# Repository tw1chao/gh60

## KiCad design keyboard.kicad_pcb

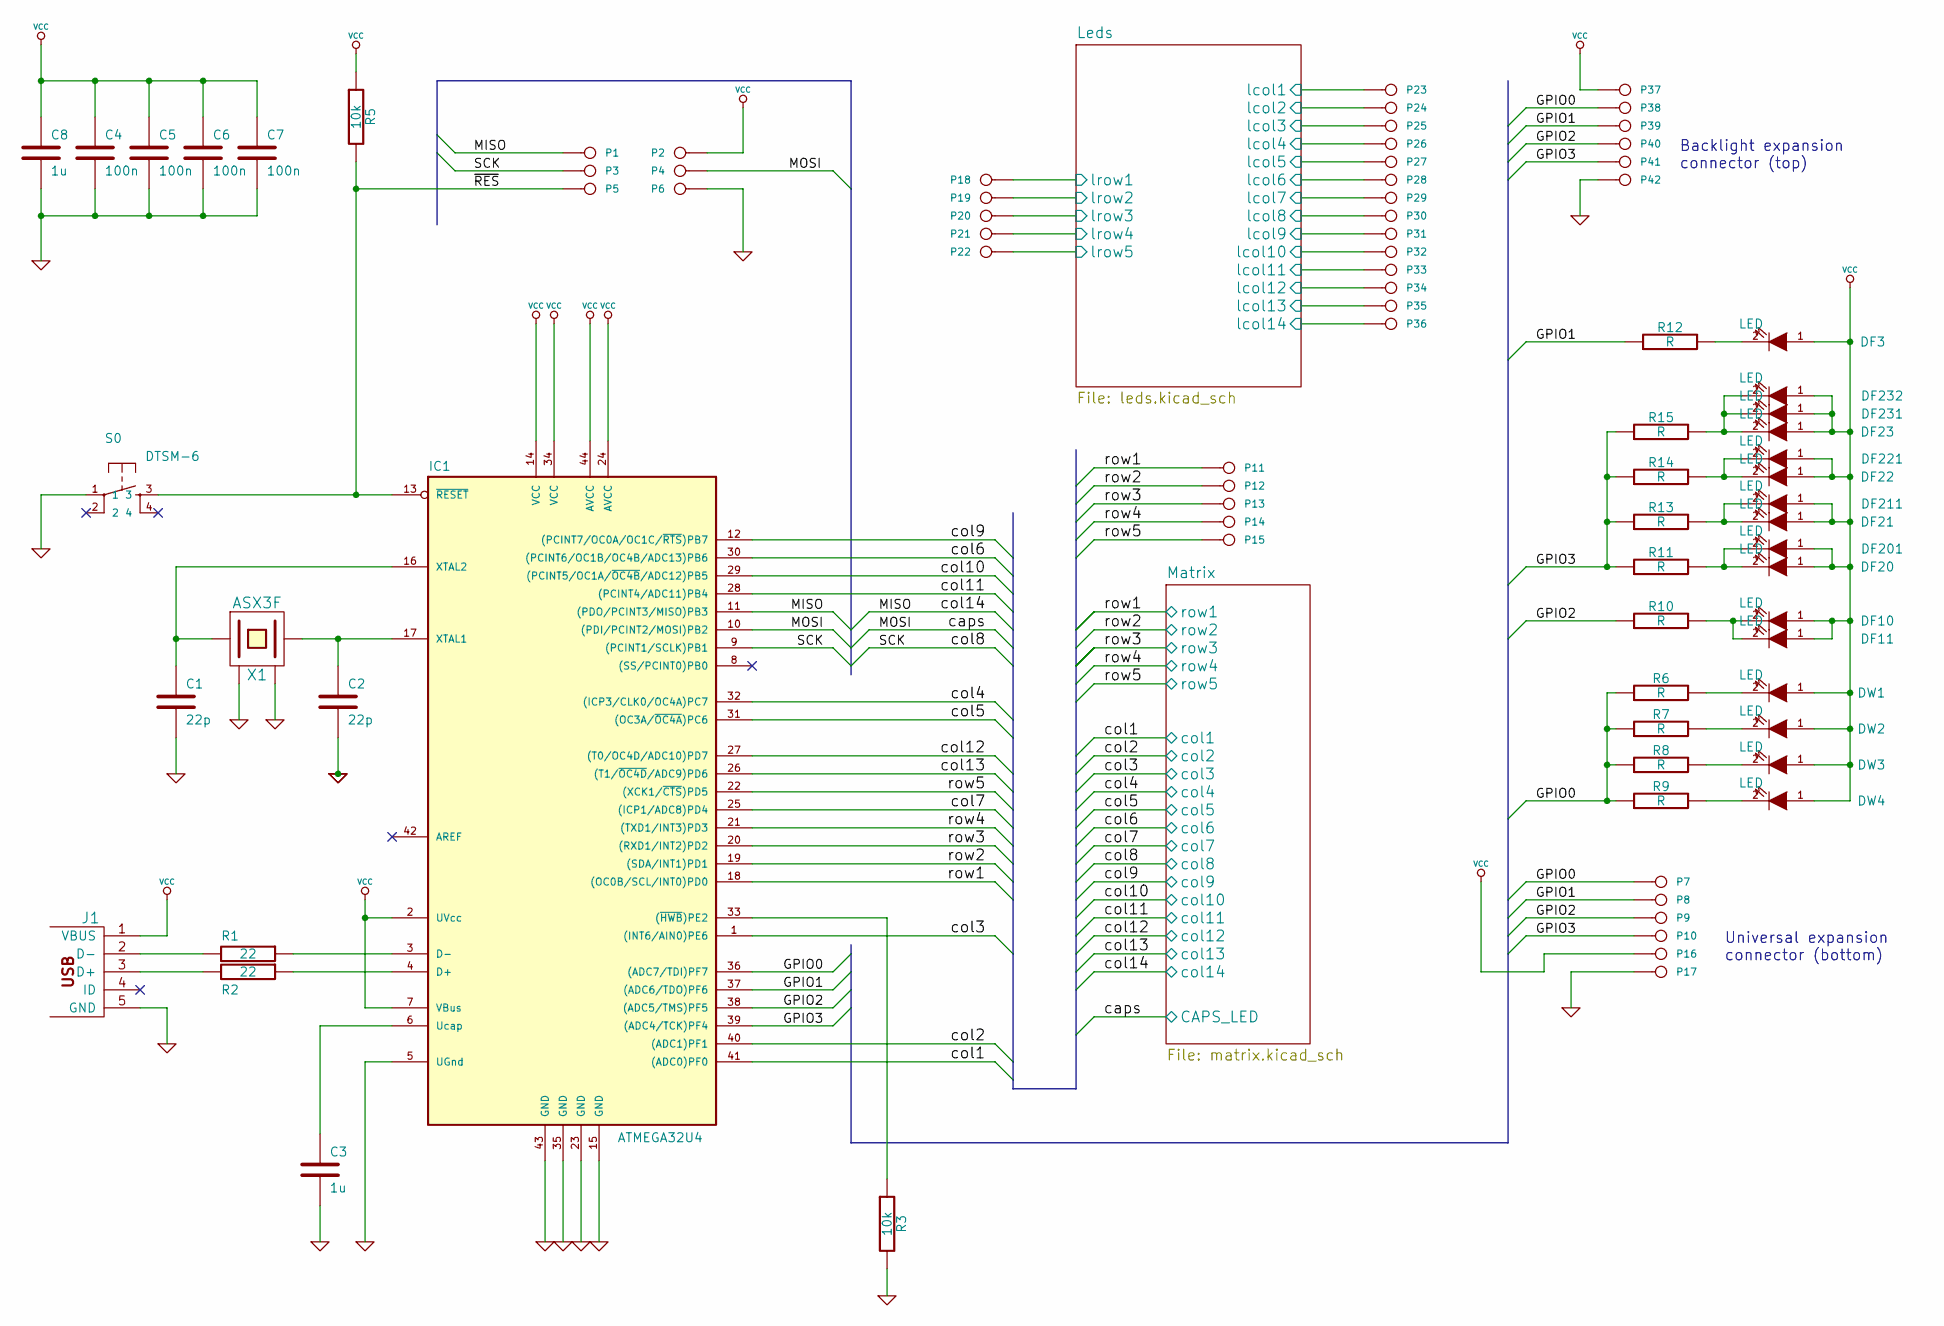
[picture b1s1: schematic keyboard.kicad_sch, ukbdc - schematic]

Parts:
C1, C2: 22p; 0805C
C3, C8: 1u; 0805C
C4, C5, C6, C7: 100n; 0805C
DF3, DF10, DF11, DF20, DF201: LED; MX1A-led_no3d
DF21, DF22, DF23, DF211, DF221, DF231, DF232: LED
DW1, DW2, DW3, DW4: LED; MX1A-led_no3d
IC1: ATMEGA32U4; TQFP44
J1: MINI; 67503
P1, P2, P3, P4, P5, P6, P7, P8, P9, P10, P11, P12, P13, P14, P15, P16, P17, P18, P19, P20, P21, P22, P23, P24, P25, P26, P27, P28, P29, P30, P31, P32, P33, P34, P35, P36, P37, P38, P39, P40, P41, P42: CONN_1
R1, R2: 22; 0805R
R3, R5: 10k; 0805R
R6, R7, R8, R9, R10, R11, R12, R13, R14, R15: R
S0: DTSM-6; KSEM31GLFS
X1: ASX3F; 4-SMD

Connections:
/GPIO0: IC1.36 ((ADC7/TDI)PF7), P7.1, P38.1, R6.1, R7.1, R8.1, R9.1
/GPIO1: IC1.37 ((ADC6/TDO)PF6), P8.1, P39.1, R12.1
/GPIO2: IC1.38 ((ADC5/TMS)PF5), P9.1, P40.1, R10.1
/GPIO3: IC1.39 ((ADC4/TCK)PF4), P10.1, P41.1, R11.1, R13.1, R14.1, R15.1
/Leds/lcol1: P23.1; also elsewhere on the board
/Leds/lcol2: P24.1; also elsewhere on the board
/Leds/lcol3: P25.1; also elsewhere on the board
/Leds/lcol4: P26.1; also elsewhere on the board
/Leds/lcol5: P27.1; also elsewhere on the board
/Leds/lcol6: P28.1; also elsewhere on the board
/Leds/lcol7: P29.1; also elsewhere on the board
/Leds/lcol8: P30.1; also elsewhere on the board
/Leds/lcol9: P31.1; also elsewhere on the board
/Leds/lcol10: P32.1; also elsewhere on the board
/Leds/lcol11: P33.1; also elsewhere on the board
/Leds/lcol12: P34.1; also elsewhere on the board
/Leds/lcol13: P35.1; also elsewhere on the board
/Leds/lcol14: P36.1; also elsewhere on the board
/Leds/lrow1: P18.1; also elsewhere on the board
/Leds/lrow2: P19.1; also elsewhere on the board
/Leds/lrow3: P20.1; also elsewhere on the board
/Leds/lrow4: P21.1; also elsewhere on the board
/Leds/lrow5: P22.1; also elsewhere on the board
/Matrix/CAPS_LED: IC1.10 ((PDI/PCINT2/MOSI)PB2), P4.1; also elsewhere on the board
/Matrix/col1: IC1.41 ((ADC0)PF0); also elsewhere on the board
/Matrix/col2: IC1.40 ((ADC1)PF1); also elsewhere on the board
/Matrix/col3: IC1.1 ((INT6/AIN0)PE6); also elsewhere on the board
/Matrix/col4: IC1.32 ((ICP3/CLK0/OC4A)PC7); also elsewhere on the board
/Matrix/col5: IC1.31 ((OC3A/~OC4A)PC6); also elsewhere on the board
/Matrix/col6: IC1.30 ((PCINT6/OC1B/OC4B/ADC13)PB6); also elsewhere on the board
/Matrix/col7: IC1.25 ((ICP1/ADC8)PD4); also elsewhere on the board
/Matrix/col8: IC1.9 ((PCINT1/SCLK)PB1), P3.1; also elsewhere on the board
/Matrix/col9: IC1.12 ((PCINT7/OC0A/OC1C/~RTS)PB7); also elsewhere on the board
/Matrix/col10: IC1.29 ((PCINT5/OC1A/~OC4B/ADC12)PB5); also elsewhere on the board
/Matrix/col11: IC1.28 ((PCINT4/ADC11)PB4); also elsewhere on the board
/Matrix/col12: IC1.27 ((T0/OC4D/ADC10)PD7); also elsewhere on the board
/Matrix/col13: IC1.26 ((T1/~OC4D/ADC9)PD6); also elsewhere on the board
/Matrix/col14: IC1.11 ((PDO/PCINT3/MISO)PB3), P1.1; also elsewhere on the board
/Matrix/row1: IC1.18 ((OC0B/SCL/INT0)PD0), P11.1; also elsewhere on the board
/Matrix/row2: IC1.19 ((SDA/INT1)PD1), P12.1; also elsewhere on the board
/Matrix/row3: IC1.20 ((RXD1/INT2)PD2), P13.1; also elsewhere on the board
/Matrix/row4: IC1.21 ((TXD1/INT3)PD3), P14.1; also elsewhere on the board
/Matrix/row5: IC1.22 ((XCK1/~CTS)PD5), P15.1; also elsewhere on the board
/~RES: IC1.13 (~RESET), P5.1, R5.2, S0.3
GND: C1.2, C2.2, C3.2, C4.2, C5.2, C6.2, C7.2, C8.2, IC1.5 (UGnd), IC1.15 (GND), IC1.23 (GND), IC1.35 (GND), IC1.43 (GND), J1.5 (GND), P6.1, P17.1, P42.1, R3.2, S0.1, X1.2 (GND), X1.4 (GND)
unnamed: C1.1, IC1.16 (XTAL2), X1.1
unnamed: DW3.2 (K), R8.2
unnamed: DW2.2 (K), R7.2
unnamed: DW1.2 (K), R6.2
unnamed: DW4.2 (K), R9.2
unnamed: IC1.33 ((~HWB)PE2), R3.1
unnamed: J1.3 (D+), R2.2
unnamed: J1.2 (D-), R1.2
unnamed: IC1.4 (D+), R2.1
unnamed: IC1.3 (D-), R1.1
unnamed: C3.1, IC1.6 (Ucap)
unnamed: C2.1, IC1.17 (XTAL1), X1.3 (2)
unnamed: DF22.2 (K), DF221.2 (K), R14.2
unnamed: DF3.2 (K), R12.2
unnamed: DF10.2 (K), DF11.2 (K), R10.2
unnamed: DF23.2 (K), DF231.2 (K), DF232.2 (K), R15.2
unnamed: DF20.2 (K), DF201.2 (K), R11.2
unnamed: DF21.2 (K), DF211.2 (K), R13.2
VCC: C4.1, C5.1, C6.1, C7.1, C8.1, DF3.1 (A), DF10.1 (A), DF11.1 (A), DF20.1 (A), DF21.1 (A), DF22.1 (A), DF23.1 (A), DF201.1 (A), DF211.1 (A), DF221.1 (A), DF231.1 (A), DF232.1 (A), DW1.1 (A), DW2.1 (A), DW3.1 (A), DW4.1 (A), IC1.2 (UVcc), IC1.7 (VBus), IC1.14 (VCC), IC1.24 (AVCC), IC1.34 (VCC), IC1.44 (AVCC), J1.1 (VBUS), P2.1, P16.1, P37.1, R5.1; also elsewhere on the board

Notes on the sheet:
Universal expansion connector (bottom)
Backlight expansion connector (top)

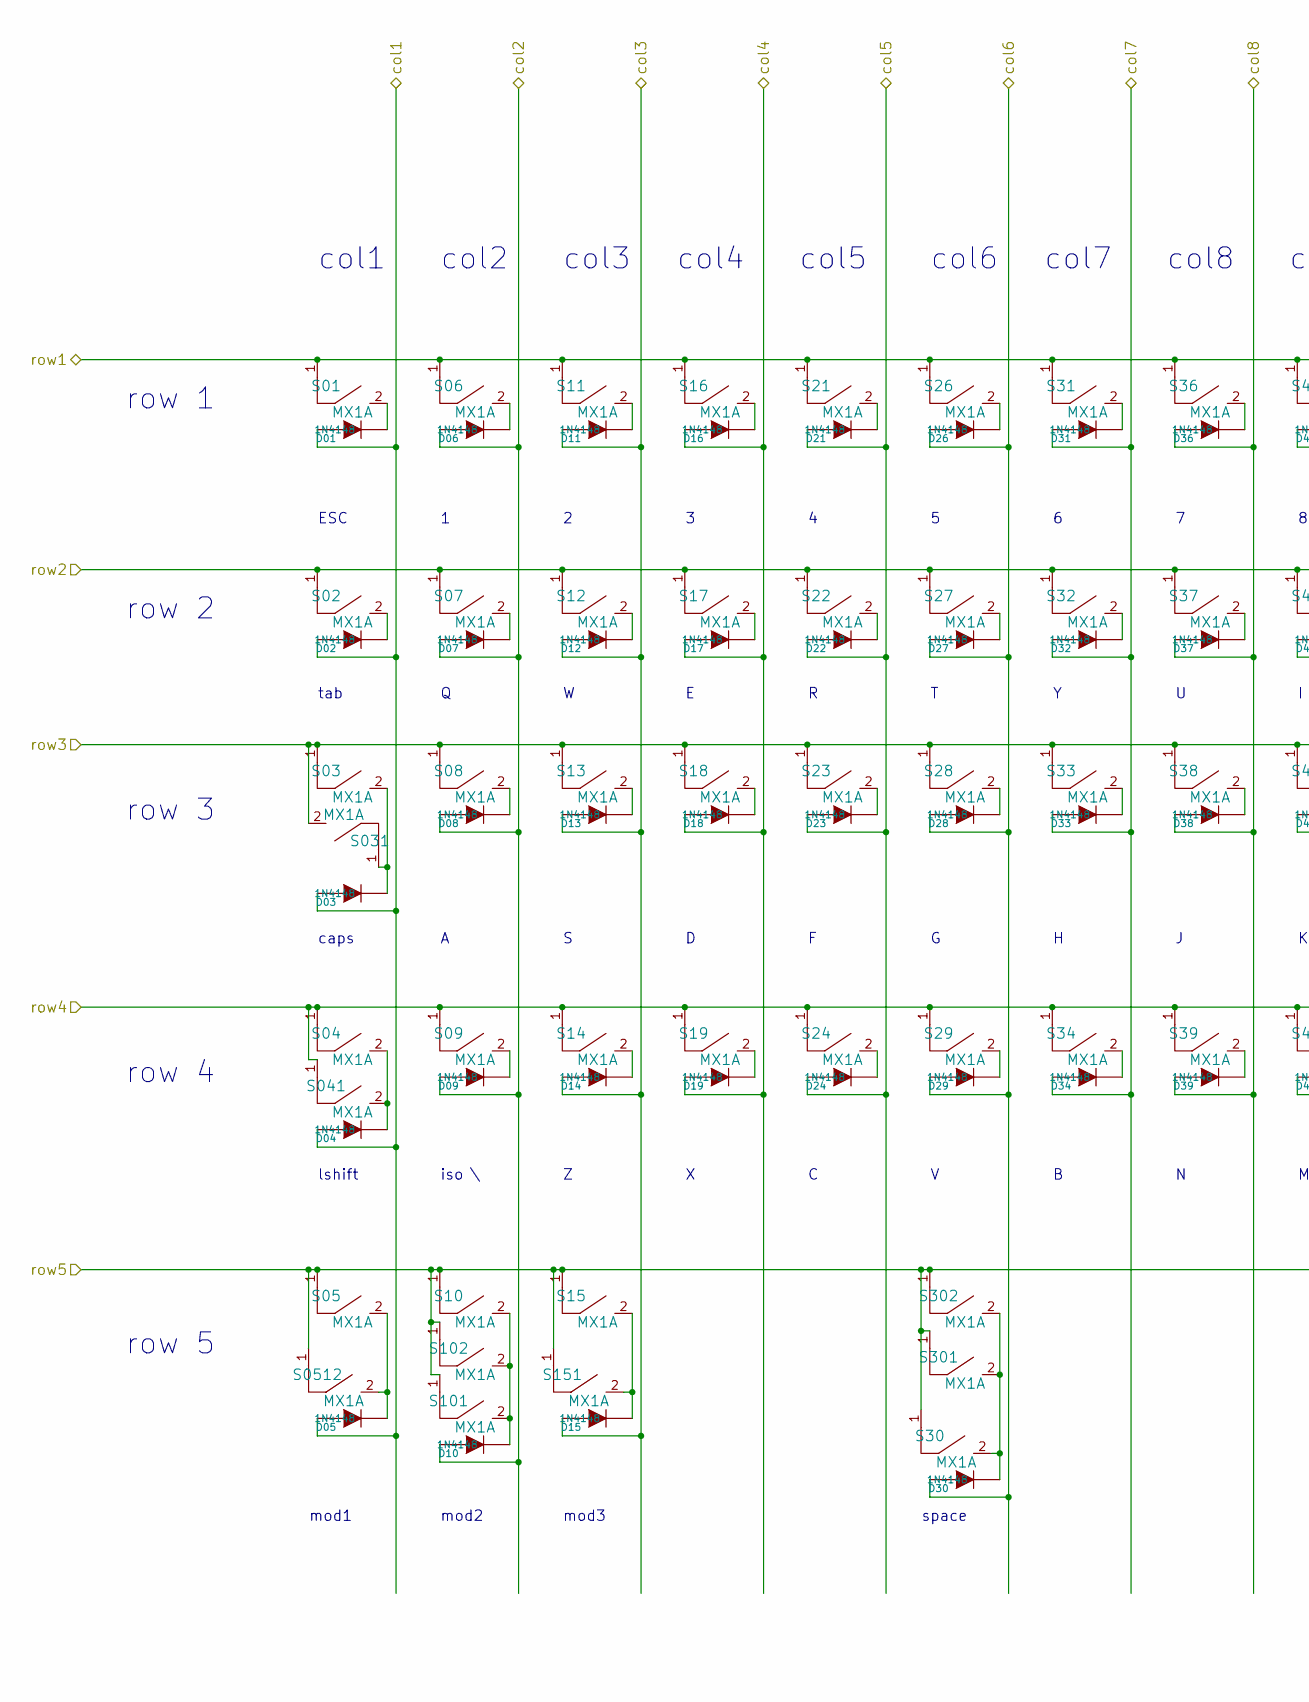
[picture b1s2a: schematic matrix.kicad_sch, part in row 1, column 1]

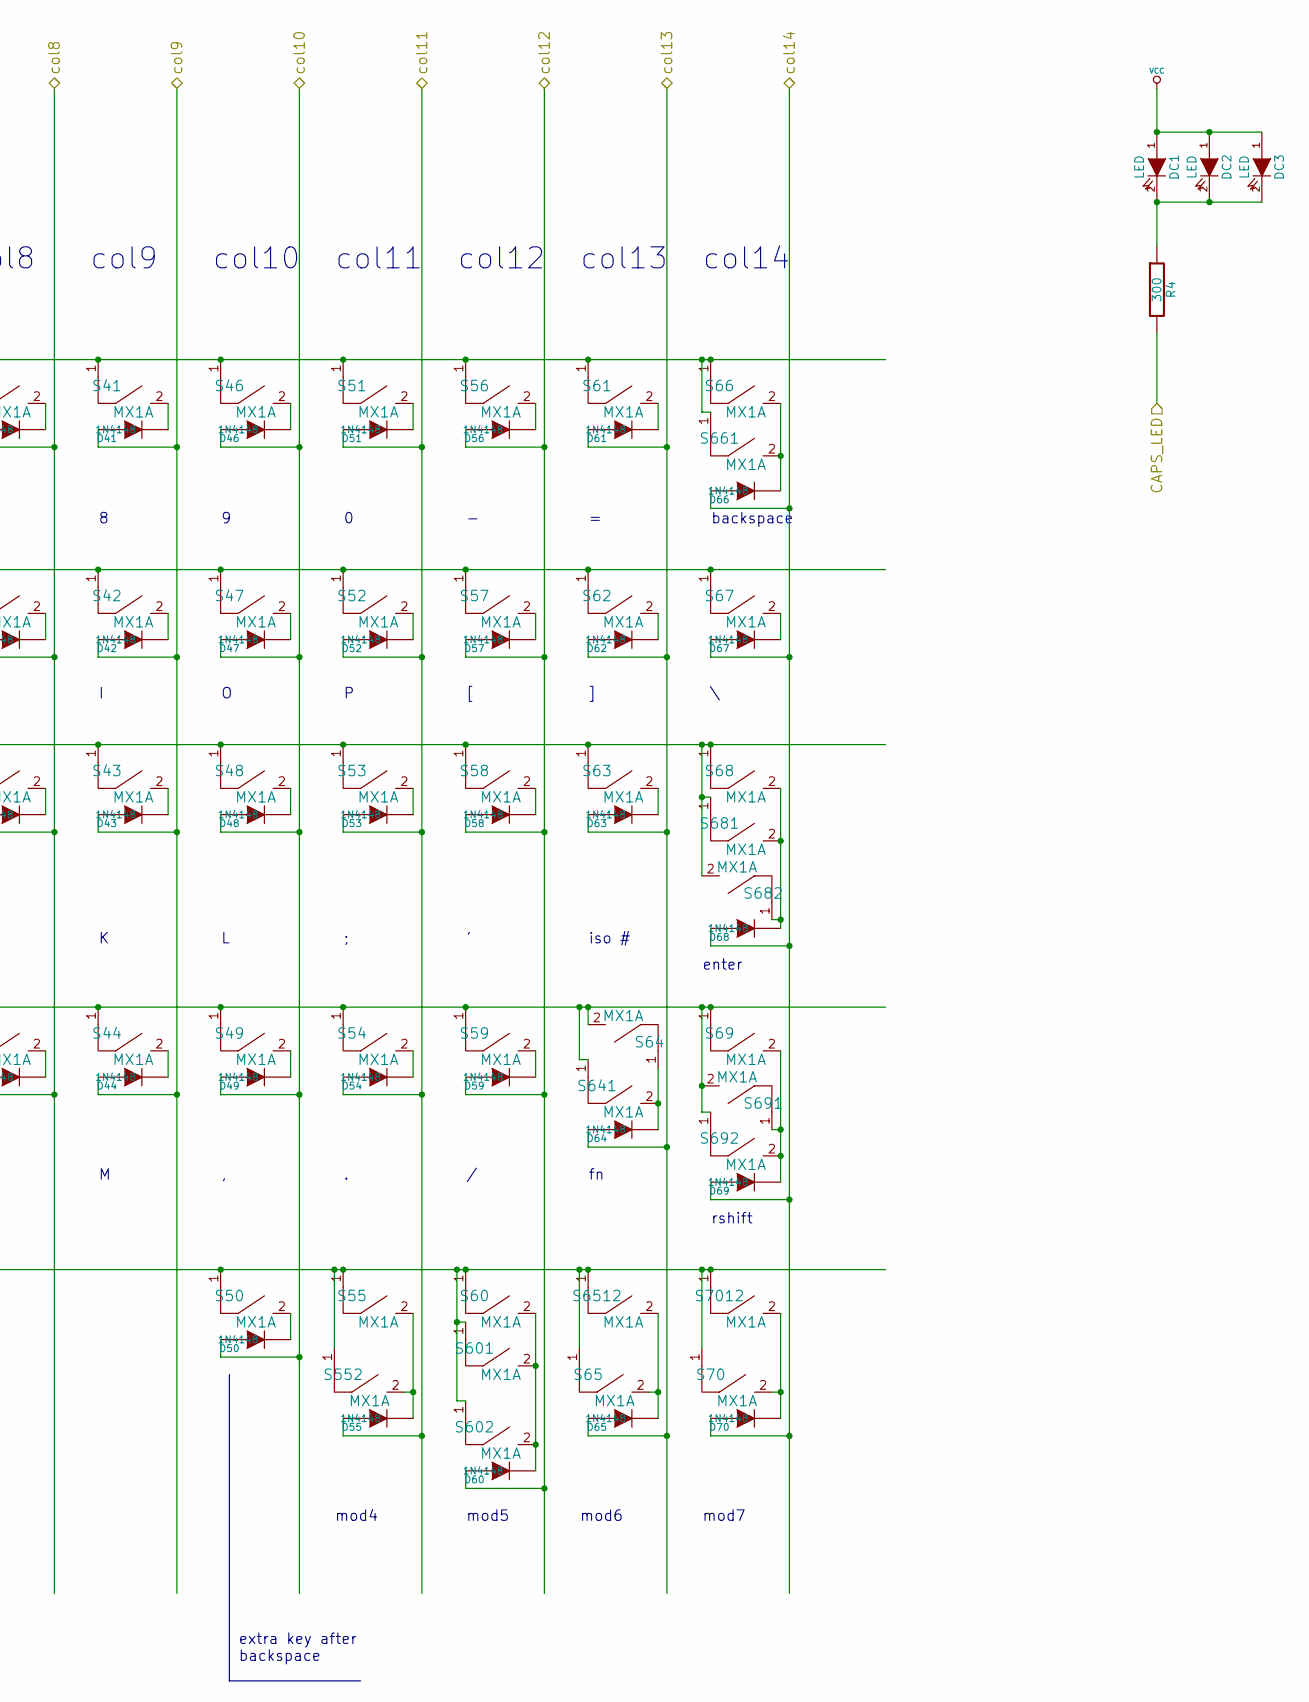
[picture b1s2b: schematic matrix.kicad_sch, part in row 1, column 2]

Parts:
D01, D02, D03, D04, D05, D06, D07, D08, D09, D10, D11, D12, D13, D14, D15, D16, D17, D18, D19, D21, D22, D23, D24, D26, D27, D28, D29, D30, D31, D32, D33, D34, D36, D37, D38, D39, D41, D42, D43, D44, D46, D47, D48, D49, D50, D51, D52, D53, D54, D55, D56, D57, D58, D59, D60, D61, D62, D63, D64, D65, D66, D67, D68, D69, D70: 1N4148; 0805D
DC1, DC2: LED; MX1A-led_no3d
DC3: LED
R4: 300
S01, S02, S03, S04, S05, S06, S07, S08, S10, S11, S12, S13, S14, S15, S16, S17, S18, S19, S21, S22, S23, S24, S26, S27, S28, S29, S30, S31, S32, S33, S34, S36, S37, S38, S39, S41, S42, S43, S44, S46, S47, S48, S49, S51, S52, S53, S54, S55, S56, S57, S58, S59, S60, S61, S62, S65, S66, S67, S68, S69, S70: MX1A
S09, S031, S041, S50, S63, S64, S101, S102, S151, S301, S302, S0512, S552, S601, S602, S641, S661, S681, S682, S691, S692, S6512, S7012: MX1A; MX1A_no3d

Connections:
/Matrix/CAPS_LED: R4.2; also elsewhere on the board
/Matrix/col1: D01.1 (A), D02.1 (A), D03.1 (A), D04.1 (A), D05.1 (A); also elsewhere on the board
/Matrix/col2: D06.1 (A), D07.1 (A), D08.1 (A), D09.1 (A), D10.1 (A); also elsewhere on the board
/Matrix/col3: D11.1 (A), D12.1 (A), D13.1 (A), D14.1 (A), D15.1 (A); also elsewhere on the board
/Matrix/col4: D16.1 (A), D17.1 (A), D18.1 (A), D19.1 (A); also elsewhere on the board
/Matrix/col5: D21.1 (A), D22.1 (A), D23.1 (A), D24.1 (A); also elsewhere on the board
/Matrix/col6: D26.1 (A), D27.1 (A), D28.1 (A), D29.1 (A), D30.1 (A); also elsewhere on the board
/Matrix/col7: D31.1 (A), D32.1 (A), D33.1 (A), D34.1 (A); also elsewhere on the board
/Matrix/col8: D36.1 (A), D37.1 (A), D38.1 (A), D39.1 (A); also elsewhere on the board
/Matrix/col9: D41.1 (A), D42.1 (A), D43.1 (A), D44.1 (A); also elsewhere on the board
/Matrix/col10: D46.1 (A), D47.1 (A), D48.1 (A), D49.1 (A), D50.1 (A); also elsewhere on the board
/Matrix/col11: D51.1 (A), D52.1 (A), D53.1 (A), D54.1 (A), D55.1 (A); also elsewhere on the board
/Matrix/col12: D56.1 (A), D57.1 (A), D58.1 (A), D59.1 (A), D60.1 (A); also elsewhere on the board
/Matrix/col13: D61.1 (A), D62.1 (A), D63.1 (A), D64.1 (A), D65.1 (A); also elsewhere on the board
/Matrix/col14: D66.1 (A), D67.1 (A), D68.1 (A), D69.1 (A), D70.1 (A); also elsewhere on the board
/Matrix/row1: S01.1, S06.1, S11.1, S16.1, S21.1, S26.1, S31.1, S36.1, S41.1, S46.1, S51.1, S56.1, S61.1, S66.1, S661.1; also elsewhere on the board
/Matrix/row2: S02.1, S07.1, S12.1, S17.1, S22.1, S27.1, S32.1, S37.1, S42.1, S47.1, S52.1, S57.1, S62.1, S67.1; also elsewhere on the board
/Matrix/row3: S03.1, S08.1, S13.1, S18.1, S23.1, S28.1, S031.2, S33.1, S38.1, S43.1, S48.1, S53.1, S58.1, S63.1, S68.1, S681.1, S682.2; also elsewhere on the board
/Matrix/row4: S04.1, S09.1, S14.1, S19.1, S24.1, S29.1, S34.1, S39.1, S041.1, S44.1, S49.1, S54.1, S59.1, S64.2, S69.1, S641.1, S691.2, S692.1; also elsewhere on the board
/Matrix/row5: S05.1, S10.1, S15.1, S30.1, S50.1, S55.1, S60.1, S65.1, S70.1, S101.1, S102.1, S151.1, S301.1, S302.1, S0512.1, S552.1, S601.1, S602.1, S6512.1, S7012.1; also elsewhere on the board
unnamed: D16.2 (K), S16.2
unnamed: D27.2 (K), S27.2
unnamed: D28.2 (K), S28.2
unnamed: D29.2 (K), S29.2
unnamed: D17.2 (K), S17.2
unnamed: D18.2 (K), S18.2
unnamed: D19.2 (K), S19.2
unnamed: D41.2 (K), S41.2
unnamed: D37.2 (K), S37.2
unnamed: D38.2 (K), S38.2
unnamed: D22.2 (K), S22.2
unnamed: D43.2 (K), S43.2
unnamed: D42.2 (K), S42.2
unnamed: D46.2 (K), S46.2
unnamed: D47.2 (K), S47.2
unnamed: D23.2 (K), S23.2
unnamed: D21.2 (K), S21.2
unnamed: D31.2 (K), S31.2
unnamed: D01.2 (K), S01.2
unnamed: D33.2 (K), S33.2
unnamed: D32.2 (K), S32.2
unnamed: D36.2 (K), S36.2
unnamed: D05.2 (K), S05.2, S0512.2
unnamed: D15.2 (K), S15.2, S151.2
unnamed: D55.2 (K), S55.2, S552.2
unnamed: D51.2 (K), S51.2
unnamed: D65.2 (K), S65.2, S6512.2
unnamed: D12.2 (K), S12.2
unnamed: D02.2 (K), S02.2
unnamed: D07.2 (K), S07.2
unnamed: D08.2 (K), S08.2
unnamed: D13.2 (K), S13.2
unnamed: D09.2 (K), S09.2
unnamed: D14.2 (K), S14.2
unnamed: D70.2 (K), S70.2, S7012.2
unnamed: D03.2 (K), S03.2, S031.1
unnamed: D26.2 (K), S26.2
unnamed: D06.2 (K), S06.2
unnamed: D11.2 (K), S11.2
unnamed: D50.2 (K), S50.2
unnamed: D63.2 (K), S63.2
unnamed: D58.2 (K), S58.2
unnamed: D53.2 (K), S53.2
unnamed: D67.2 (K), S67.2
unnamed: D52.2 (K), S52.2
unnamed: D48.2 (K), S48.2
unnamed: D44.2 (K), S44.2
unnamed: D62.2 (K), S62.2
unnamed: D49.2 (K), S49.2
unnamed: D54.2 (K), S54.2
unnamed: D59.2 (K), S59.2
unnamed: D57.2 (K), S57.2
unnamed: D61.2 (K), S61.2
unnamed: D56.2 (K), S56.2
unnamed: D24.2 (K), S24.2
unnamed: D34.2 (K), S34.2
unnamed: D39.2 (K), S39.2
unnamed: D68.2 (K), S68.2, S681.2, S682.1
unnamed: D10.2 (K), S10.2, S101.2, S102.2
unnamed: D30.2 (K), S30.2, S301.2, S302.2
unnamed: D04.2 (K), S04.2, S041.2
unnamed: D64.2 (K), S64.1, S641.2
unnamed: D69.2 (K), S69.2, S691.1, S692.2
unnamed: DC1.2 (K), DC2.2 (K), DC3.2 (K), R4.1
unnamed: D60.2 (K), S60.2, S601.2, S602.2
unnamed: D66.2 (K), S66.2, S661.2
VCC: DC1.1 (A), DC2.1 (A), DC3.1 (A); also elsewhere on the board

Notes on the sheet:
space
col6
ESC
mod5
col5
col13
col10
col4
row 4
mod7
lshift
iso \
tab
col12
mod1
mod4
iso #
rshift
row 1
enter
col14
col8
col11
mod2
col7
col2
backspace
extra key after backspace
col1
row 2
row 5
col3
mod3
caps
col9
mod6
row 3

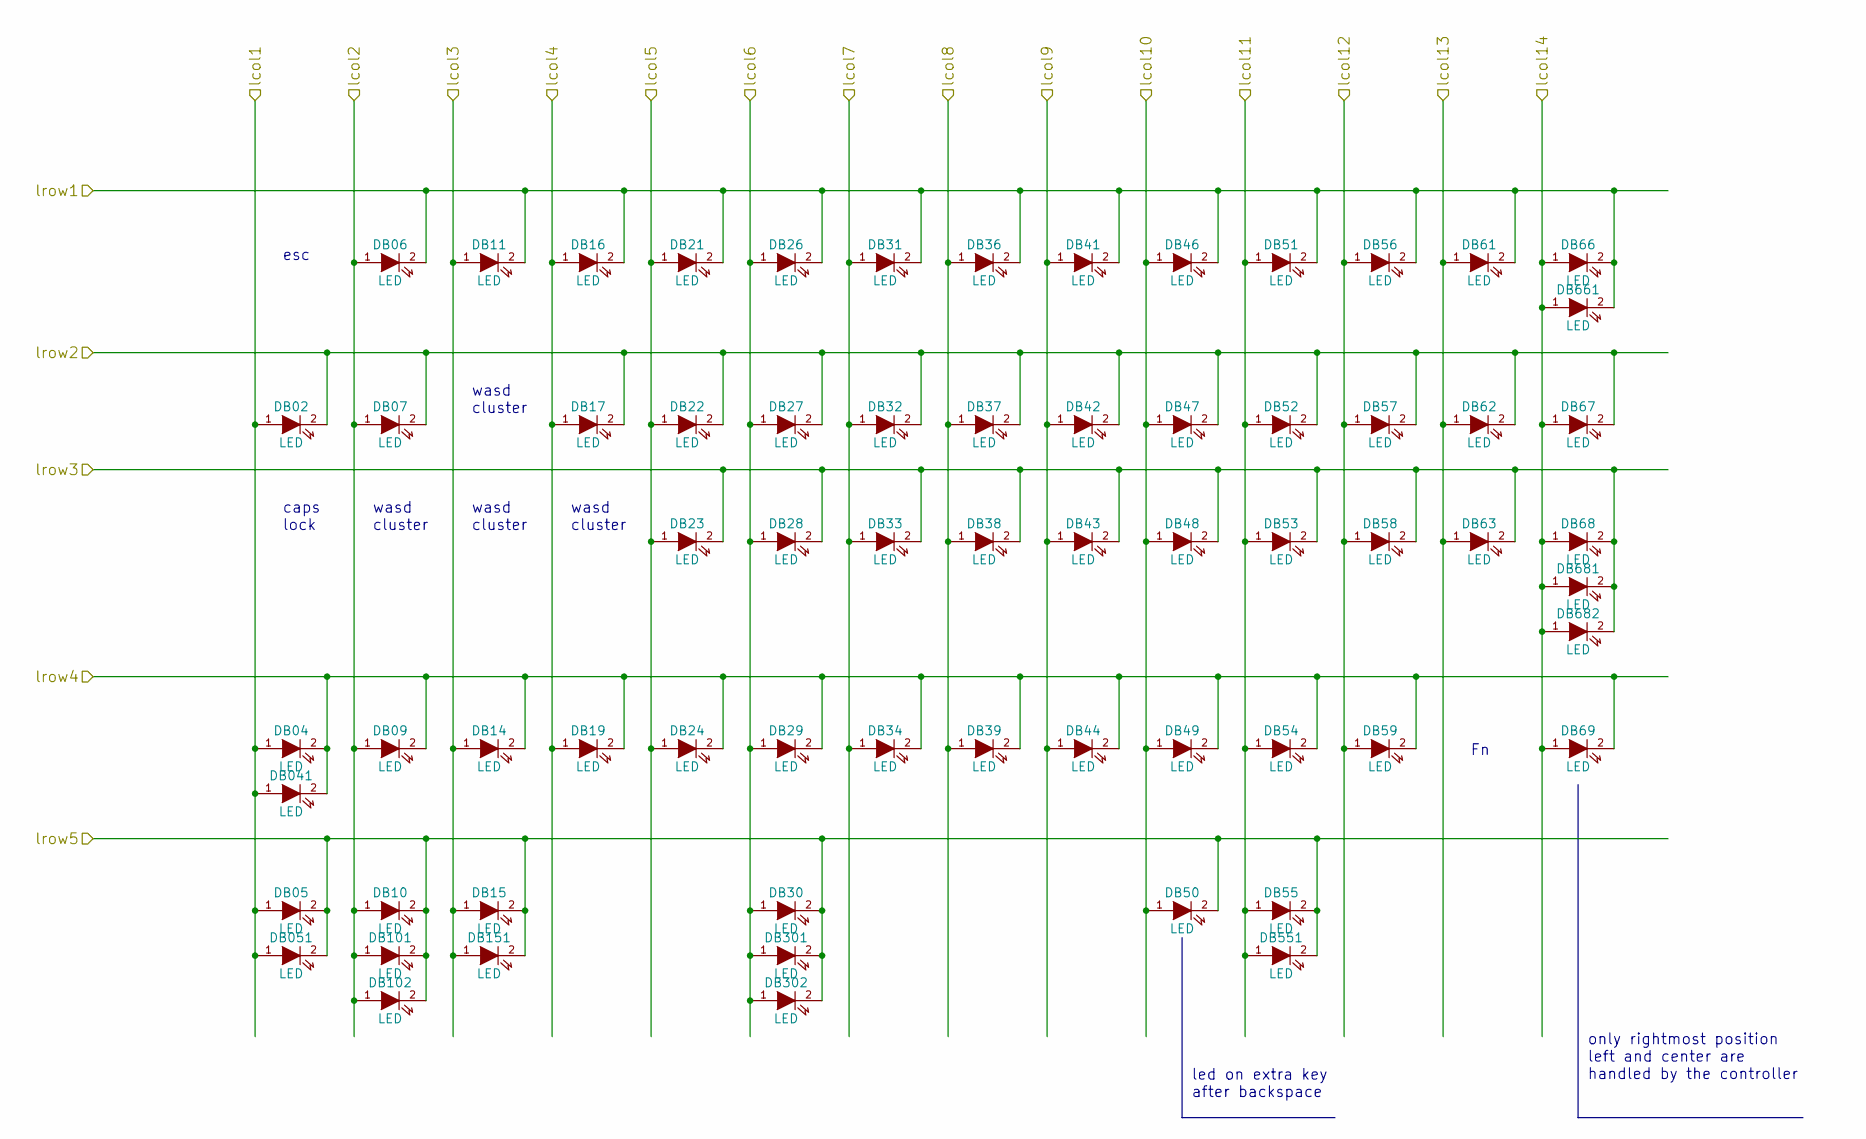
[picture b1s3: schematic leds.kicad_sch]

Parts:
DB02, DB04, DB06, DB07, DB09, DB11, DB14, DB16, DB17, DB19, DB21, DB22, DB23, DB24, DB26, DB27, DB28, DB29, DB30, DB31, DB32, DB33, DB34, DB36, DB37, DB38, DB39, DB41, DB041, DB42, DB43, DB44, DB46, DB47, DB48, DB49, DB50, DB51, DB52, DB53, DB54, DB56, DB57, DB58, DB59, DB61, DB62, DB63, DB66, DB67, DB68, DB69, DB301, DB302, DB661, DB681, DB682: LED; MX1A-led_no3d
DB05, DB10, DB15, DB051, DB55, DB101, DB102, DB151, DB551: LED

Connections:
/Leds/lcol1: DB02.1 (A), DB04.1 (A), DB05.1 (A), DB041.1 (A), DB051.1 (A); also elsewhere on the board
/Leds/lcol2: DB06.1 (A), DB07.1 (A), DB09.1 (A), DB10.1 (A), DB101.1 (A), DB102.1 (A); also elsewhere on the board
/Leds/lcol3: DB11.1 (A), DB14.1 (A), DB15.1 (A), DB151.1 (A); also elsewhere on the board
/Leds/lcol4: DB16.1 (A), DB17.1 (A), DB19.1 (A); also elsewhere on the board
/Leds/lcol5: DB21.1 (A), DB22.1 (A), DB23.1 (A), DB24.1 (A); also elsewhere on the board
/Leds/lcol6: DB26.1 (A), DB27.1 (A), DB28.1 (A), DB29.1 (A), DB30.1 (A), DB301.1 (A), DB302.1 (A); also elsewhere on the board
/Leds/lcol7: DB31.1 (A), DB32.1 (A), DB33.1 (A), DB34.1 (A); also elsewhere on the board
/Leds/lcol8: DB36.1 (A), DB37.1 (A), DB38.1 (A), DB39.1 (A); also elsewhere on the board
/Leds/lcol9: DB41.1 (A), DB42.1 (A), DB43.1 (A), DB44.1 (A); also elsewhere on the board
/Leds/lcol10: DB46.1 (A), DB47.1 (A), DB48.1 (A), DB49.1 (A), DB50.1 (A); also elsewhere on the board
/Leds/lcol11: DB51.1 (A), DB52.1 (A), DB53.1 (A), DB54.1 (A), DB55.1 (A), DB551.1 (A); also elsewhere on the board
/Leds/lcol12: DB56.1 (A), DB57.1 (A), DB58.1 (A), DB59.1 (A); also elsewhere on the board
/Leds/lcol13: DB61.1 (A), DB62.1 (A), DB63.1 (A); also elsewhere on the board
/Leds/lcol14: DB66.1 (A), DB67.1 (A), DB68.1 (A), DB69.1 (A), DB661.1 (A), DB681.1 (A), DB682.1 (A); also elsewhere on the board
/Leds/lrow1: DB06.2 (K), DB11.2 (K), DB16.2 (K), DB21.2 (K), DB26.2 (K), DB31.2 (K), DB36.2 (K), DB41.2 (K), DB46.2 (K), DB51.2 (K), DB56.2 (K), DB61.2 (K), DB66.2 (K), DB661.2 (K); also elsewhere on the board
/Leds/lrow2: DB02.2 (K), DB07.2 (K), DB17.2 (K), DB22.2 (K), DB27.2 (K), DB32.2 (K), DB37.2 (K), DB42.2 (K), DB47.2 (K), DB52.2 (K), DB57.2 (K), DB62.2 (K), DB67.2 (K); also elsewhere on the board
/Leds/lrow3: DB23.2 (K), DB28.2 (K), DB33.2 (K), DB38.2 (K), DB43.2 (K), DB48.2 (K), DB53.2 (K), DB58.2 (K), DB63.2 (K), DB68.2 (K), DB681.2 (K), DB682.2 (K); also elsewhere on the board
/Leds/lrow4: DB04.2 (K), DB09.2 (K), DB14.2 (K), DB19.2 (K), DB24.2 (K), DB29.2 (K), DB34.2 (K), DB39.2 (K), DB041.2 (K), DB44.2 (K), DB49.2 (K), DB54.2 (K), DB59.2 (K), DB69.2 (K); also elsewhere on the board
/Leds/lrow5: DB05.2 (K), DB10.2 (K), DB15.2 (K), DB30.2 (K), DB50.2 (K), DB051.2 (K), DB55.2 (K), DB101.2 (K), DB102.2 (K), DB151.2 (K), DB301.2 (K), DB302.2 (K), DB551.2 (K); also elsewhere on the board

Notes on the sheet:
wasd cluster
caps lock
esc
only rightmost position left and center are handled by the controller
led on extra key after backspace

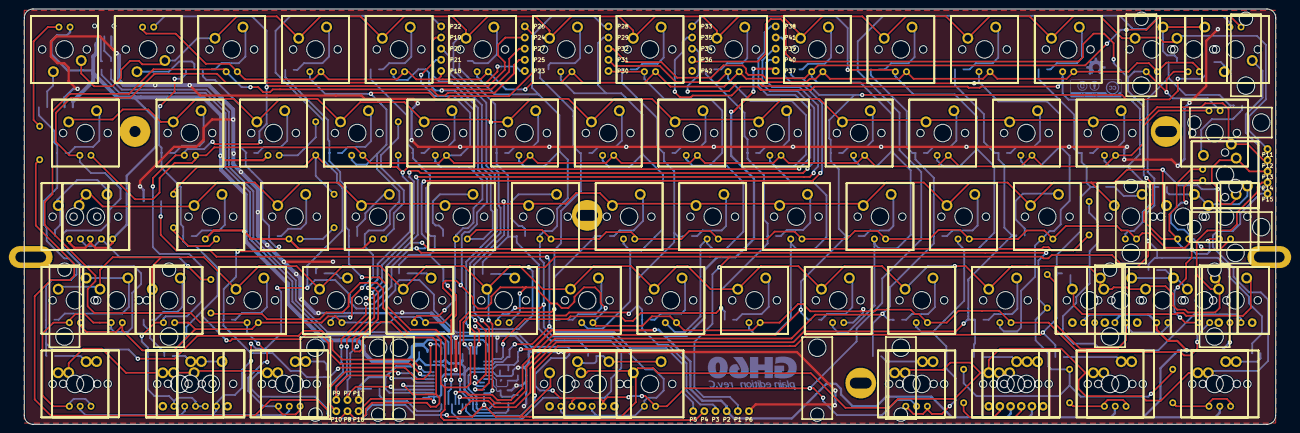
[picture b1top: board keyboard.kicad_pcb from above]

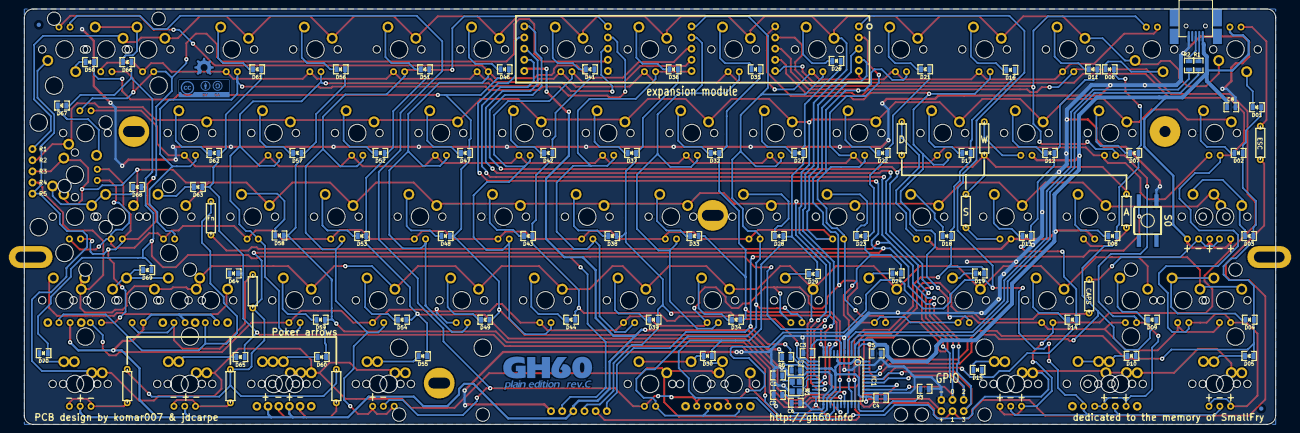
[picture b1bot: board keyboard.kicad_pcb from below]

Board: 2 copper layers, 285.0 x 94.6 mm, 335 parts (94 on the bottom side), 130 nets.

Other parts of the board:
FID: FIDUCIAL
FID#2: FIDUCIAL
HOLE: VAL**; PKRHSL
HOLE#2, HOLE#4, HOLE#6: VAL**; PKRH
HOLE#3: VAL**; PKRHSL
HOLE#5: VAL**; PKRHC
MXST: VAL**; MXST
MXST#2, MXST#3, MXST#4, MXST#5, MXST#6, MXST#7, MXST#8, MXST#9, MXST#10, MXST#11, MXST#12, MXST#13, MXST#14, MXST#15: VAL**; MXST
MXWIRE: VAL**; MX1A-wire
MXWIRE#2, MXWIRE#3, MXWIRE#4, MXWIRE#5, MXWIRE#6, MXWIRE#7, MXWIRE#8, MXWIRE#9: VAL**; MX1A-wire

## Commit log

2022-04-04 support kicad ver 6.0.2-0
